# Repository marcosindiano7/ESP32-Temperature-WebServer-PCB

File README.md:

# ESP32 Temperature Web Server PCB

Custom two-layer PCB designed in KiCad for an ESP32-based temperature monitoring system.  
The board measures temperature using an LM35 analog sensor and allows the measured value to be monitored through a web interface served by the ESP32 module.

This project focuses on the complete hardware development flow: schematic capture, PCB layout, manufacturing files generation, board assembly and laboratory validation.

## Project Overview

The goal of this project was to design and validate a functional printed circuit board for an IoT temperature monitoring device.

The system includes:

- ESP32 module as the main processing and communication unit
- LM35 analog temperature sensor
- USB-to-UART interface based on CH340N
- RS232 communication interface
- Communication selection through jumpers
- 5 V regulated power supply stage
- Bootloader and reset management circuitry
- Alarm LED output
- Expansion connector for additional ESP32 signals
- Two-layer PCB designed in KiCad
- SMD and through-hole component assembly
- Laboratory functional validation

## PCB Preview

### 3D Render

### PCB Layout

### Assembled Board

### Web Interface

## Hardware Architecture

The schematic is divided into several functional blocks:

### Power Regulation

The power stage provides the regulated supply required by the system.  
It includes input filtering, a linear voltage regulator and a power indicator LED.

### ESP32 Module

The ESP32 module acts as the core of the system.  
It is connected to the temperature sensing stage, UART communication lines, boot/reset circuitry and alarm LED.

### Temperature Sensor

The board uses an LM35 analog temperature sensor.  
Its output voltage is proportional to the measured temperature and is connected to the ESP32 analog input through a simple conditioning/filtering stage.

### USB Interface

A CH340N USB-to-UART converter is used to provide serial communication through the USB connector.

### RS232 Interface

The board also includes an RS232 communication stage with level adaptation to interface with the ESP32 UART signals.

### Communication Selection

Jumpers are used to select whether the ESP32 UART lines are connected to the USB interface or to the RS232 interface.

### Bootloader and Reset Management

The design includes manual and automatic boot/reset circuitry, allowing the ESP32 to start normally or enter programming mode.

### Expansion Connector

An expansion connector exposes additional ESP32 pins for future extensions or external peripherals.

## Repository Structure

```text
.
├── hardware/
│   ├── kicad/              # KiCad project files
│   └── fabrication/        # Gerber and drill files
├── docs/
│   └── images/             # Schematic captures, PCB renders and photos
├── bom/                    # Bill of materials, if available
├── README.md
└── .gitignore
```

## KiCad Design

The hardware design was developed using KiCad and includes:

- Schematic capture
- Custom symbol/footprint handling
- Two-layer PCB layout
- Functional block-based component placement
- Top and bottom copper zones connected to GND
- SMD and through-hole component placement
- Mounting holes
- Silkscreen identification
- Design files ready for manufacturing

## Manufacturing Files

The `hardware/fabrication/` folder contains the production files required to manufacture the PCB:

- Top and bottom copper layers
- Top and bottom solder mask
- Top and bottom silkscreen
- Solder paste layers
- Board outline
- PTH and NPTH drill files
- Gerber job file

## Assembly

The PCB was manufactured externally and later assembled in the laboratory.  
The assembly process included both SMD and through-hole components.

Main assembled elements:

- ESP32 socket/header area
- USB connector
- DB9 RS232 connector
- Voltage regulator
- CH340N USB-to-UART converter
- LM35 temperature sensor socket
- BJTs and diode-based interface circuitry
- Jumpers and test points
- Indicator LEDs
- Mounting holes

## Validation

The assembled PCB was validated through several checks:

- Power supply verification
- 5 V regulator output measurement
- ESP32 module power-up test
- USB communication test
- RS232 communication test
- UART signal routing through jumpers
- Web server access from a mobile browser
- Temperature visualization
- Configurable threshold test
- Alarm LED activation when the temperature exceeds the configured threshold

## Functional Test

During the final test, the ESP32 web interface displayed:

- Current time
- Measured temperature
- Configurable temperature threshold
- Alarm message when the threshold was exceeded
- Button to clear the alert

Example web interface:

## Skills Demonstrated

- PCB design with KiCad
- Schematic capture
- PCB layout and routing
- Gerber and drill file generation
- SMD soldering
- Through-hole soldering
- ESP32-based IoT hardware
- Analog sensor integration
- USB-to-UART communication
- RS232 interface design
- Boot/reset circuit integration
- Laboratory hardware validation
- Multimeter and oscilloscope-based testing
- Technical documentation

## Notes

This repository focuses on the hardware design, PCB manufacturing files and validation process.  
Firmware or software not originally developed by the author is not included.

## Author

Marcos Indiano  
Electronic Communications Engineering student  
Universidad Politécnica de Madrid

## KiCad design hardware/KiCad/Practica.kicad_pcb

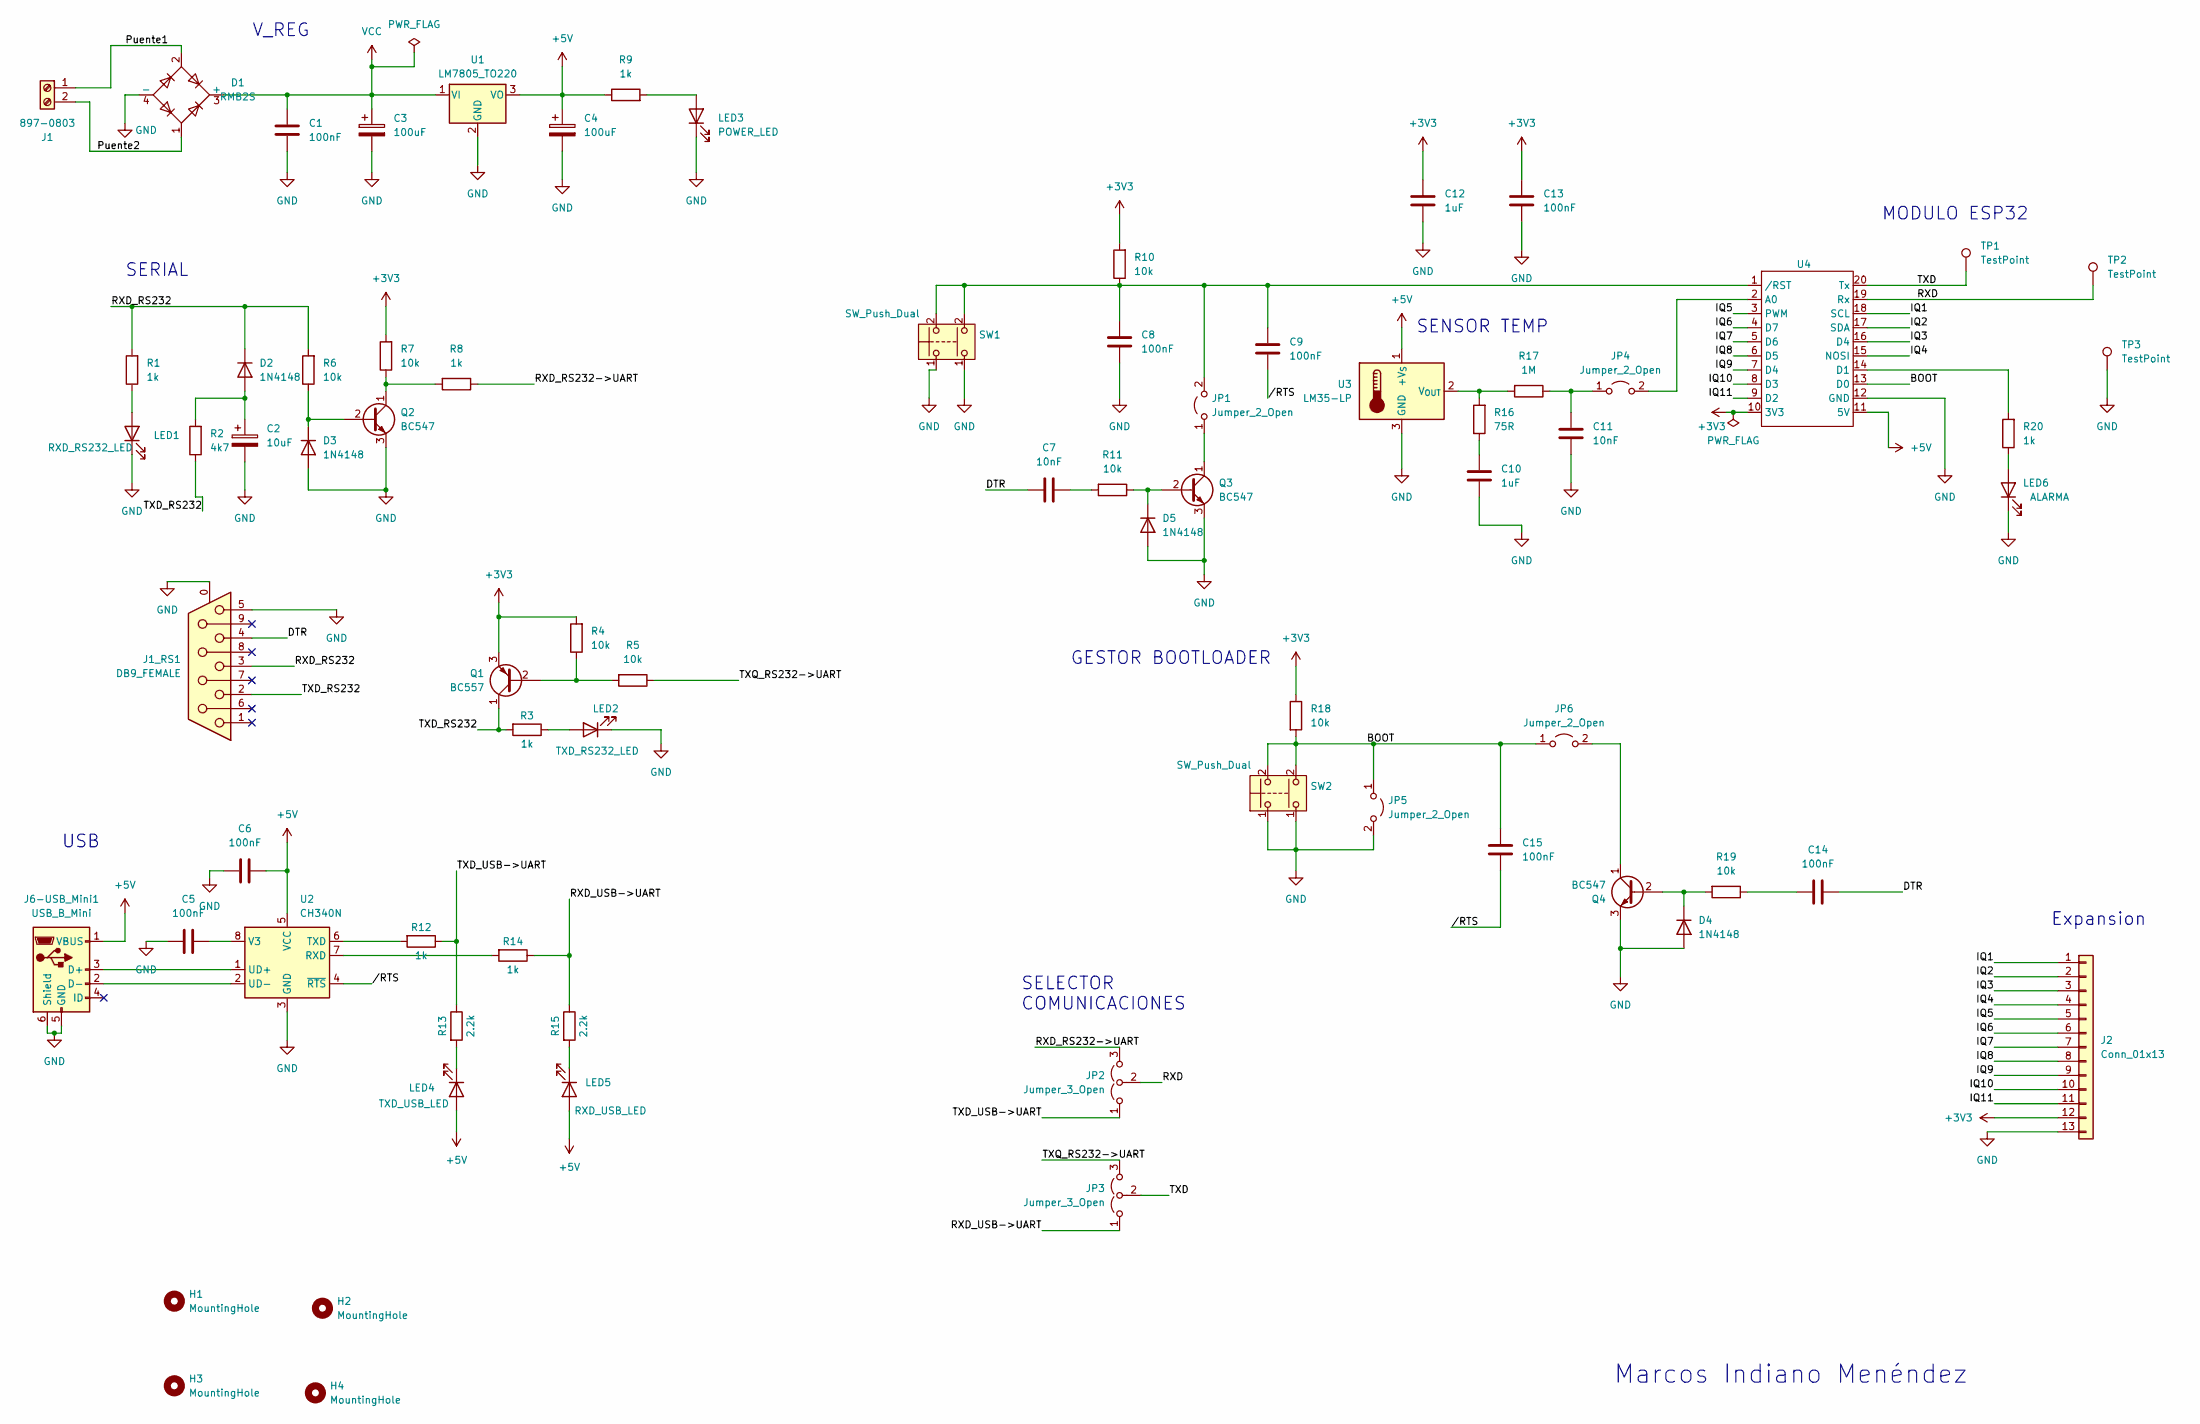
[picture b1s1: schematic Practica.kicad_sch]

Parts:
C1, C5, C6, C8, C9, C13, C14, C15: 100nF; C_1206_3216Metric
C2: 10uF; C_1206_3216Metric
C3, C4: 100uF; CP_Radial_D5.0mm_P2.50mm
C7, C11: 10nF; C_1206_3216Metric
C10, C12: 1uF; C_1206_3216Metric
D1: RMB2S; TO-269AA
D2, D3, D4, D5: 1N4148; D_DO-35_SOD27_P7.62mm_Horizontal
H1, H2, H3, H4: MountingHole; MountingHole_3mm_Pad
J1: 897-0803; TerminalBlock_RND_205-00276_1x02_P5.00mm_Vertical
J1_RS1: DB9_FEMALE; DSUB-9_Female_Horizontal_P2.77x2.84mm_EdgePinOffset4.94mm_H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
J2: Conn_01x13; PinHeader_1x13_P2.54mm_Vertical
J6-USB_Mini1: USB_B_Mini; USB_Mini-B_Wuerth_65100516121_Horizontal
JP1, JP4, JP5, JP6: Jumper_2_Open; PinHeader_1x02_P2.54mm_Vertical
JP2, JP3: Jumper_3_Open; PinHeader_1x03_P2.54mm_Vertical
LED1: RXD_RS232_LED; LED_D3.0mm
LED2: TXD_RS232_LED; LED_D3.0mm
LED3: POWER_LED; LED_D3.0mm
LED4: TXD_USB_LED; LED_D3.0mm
LED5: RXD_USB_LED; LED_D3.0mm
LED6: ALARMA; LED_D3.0mm
Q1: BC557; TO-92_Inline
Q2, Q3, Q4: BC547; TO-92_Inline_Wide
R1, R3, R8, R9, R12, R14, R20: 1k; R_1206_3216Metric
R2: 4k7; R_1206_3216Metric
R4, R5, R6, R7, R10, R11, R18, R19: 10k; R_1206_3216Metric
R13, R15: 2.2k; R_1206_3216Metric
R16: 75R; R_1206_3216Metric
R17: 1M; R_1206_3216Metric
SW1, SW2: SW_Push_Dual; SW_SPST_B3S-1000
TP1, TP2, TP3: TestPoint; TestPoint_THTPad_1.5x1.5mm_Drill0.7mm
U1: LM7805_TO220; TO-220-3_Vertical
U2: CH340N; SOP-8_3.9x4.9mm_P1.27mm
U3: LM35-LP; TO-92_Inline_Wide
U4: ESP32

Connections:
+3V3: C12.1, C13.1, J2.12, Q1.3 (E), R4.2, R7.2, R10.2, R18.1, U4.10 (3V3)
+5V: C4.1, C6.2, J6-USB_Mini1.1 (VBUS), LED4.2 (A), LED5.2 (A), R9.1, U1.3 (VO), U2.5 (VCC), U3.1 (+V_{S}), U4.11 (5V)
/BOOT: C15.2, JP5.1 (A), JP6.1 (A), R18.2, SW2.2 (4), U4.13 (D0)
/DTR: C7.1, C14.2, J1_RS1.4
/IQ1: J2.1, U4.18 (SCL)
/IQ2: J2.2, U4.17 (SDA)
/IQ3: J2.3, U4.16 (D4)
/IQ4: J2.4, U4.15 (NOSI)
/IQ5: J2.5, U4.3 (PWM)
/IQ6: J2.6, U4.4 (D7)
/IQ7: J2.7, U4.5 (D6)
/IQ8: J2.8, U4.6 (D5)
/IQ9: J2.9, U4.7 (D4)
/IQ10: J2.10, U4.8 (D3)
/IQ11: J2.11, U4.9 (D2)
/Puente1: D1.2, J1.1
/Puente2: D1.1, J1.2
/RXD: JP2.2 (C), TP2.1, U4.19 (Rx)
/RXD_RS232: D2.1 (K), J1_RS1.3, R1.2, R6.2
/RXD_RS232->UART: JP2.3 (B), R8.1
/RXD_USB->UART: JP3.1 (A), R14.1, R15.1
/TXD: JP3.2 (C), TP1.1, U4.20 (Tx)
/TXD_RS232: J1_RS1.2, Q1.1 (C), R2.1, R3.2
/TXD_USB->UART: JP2.1 (A), R12.1, R13.1
/TXQ_RS232->UART: JP3.3 (B), R5.1
//RTS: C9.2, C15.1, U2.4 (~RTS)
GND: C1.2, C2.2, C3.2, C4.2, C5.1, C6.1, C8.2, C10.2, C11.2, C12.2, C13.2, D1.4 (-), D3.2 (A), D4.2 (A), D5.2 (A), J1_RS1.0 (PAD), J1_RS1.5, J2.13, J6-USB_Mini1.5 (GND), J6-USB_Mini1.6 (Shield), JP5.2 (B), LED1.1 (K), LED2.1 (K), LED3.1 (K), LED6.1 (K), Q2.3 (E), Q3.3 (E), Q4.3 (E), SW1.1, SW2.1, TP3.1, U1.2 (GND), U2.3 (GND), U3.3 (GND), U4.12 (GND)
unnamed: C7.2, R11.2
unnamed: C10.1, R16.1
unnamed: C14.1, R19.1
unnamed: C2.1, D2.2 (A), R2.2
unnamed: D3.1 (K), Q2.2 (B), R6.1
unnamed: D4.1 (K), Q4.2 (B), R19.2
unnamed: D5.1 (K), Q3.2 (B), R11.1
unnamed: J6-USB_Mini1.3 (D+), U2.1 (UD+)
unnamed: J6-USB_Mini1.2 (D-), U2.2 (UD-)
unnamed: JP1.1 (A), Q3.1 (C)
unnamed: C8.1, C9.1, JP1.2 (B), R10.1, SW1.2, U4.1 (/RST)
unnamed: C11.1, JP4.1 (A), R17.1
unnamed: JP4.2 (B), U4.2 (A0)
unnamed: JP6.2 (B), Q4.1 (C)
unnamed: LED1.2 (A), R1.1
unnamed: LED2.2 (A), R3.1
unnamed: LED3.2 (A), R9.2
unnamed: LED4.1 (K), R13.2
unnamed: LED5.1 (K), R15.2
unnamed: LED6.2 (A), R20.1
unnamed: Q1.2 (B), R4.1, R5.2
unnamed: Q2.1 (C), R7.1, R8.2
unnamed: R14.2, U2.7 (RXD)
unnamed: R12.2, U2.6 (TXD)
unnamed: C5.2, U2.8 (V3)
unnamed: R16.2, R17.2, U3.2 (V_{OUT})
unnamed: R20.2, U4.14 (D1)
VCC: C1.1, C3.1, D1.3 (+), U1.1 (VI)

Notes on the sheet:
SELECTOR COMUNICACIONES
SERIAL
Marcos Indiano Menéndez
SENSOR TEMP
Expansion
USB
V_REG
MODULO ESP32
GESTOR BOOTLOADER

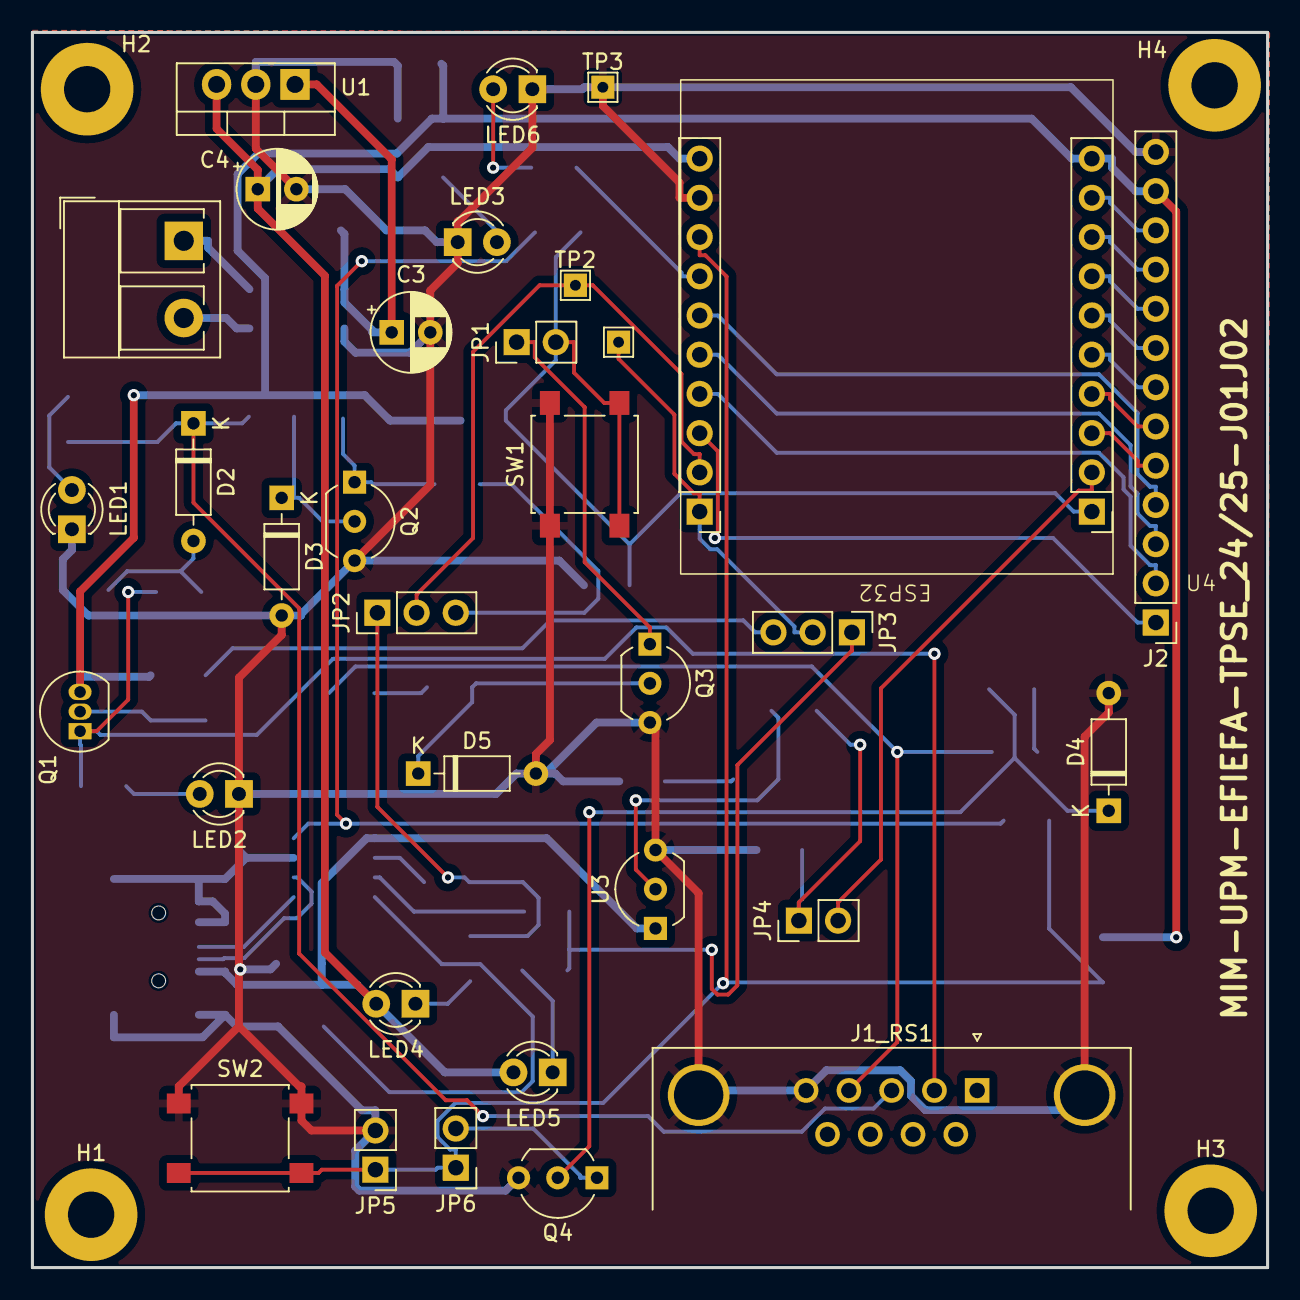
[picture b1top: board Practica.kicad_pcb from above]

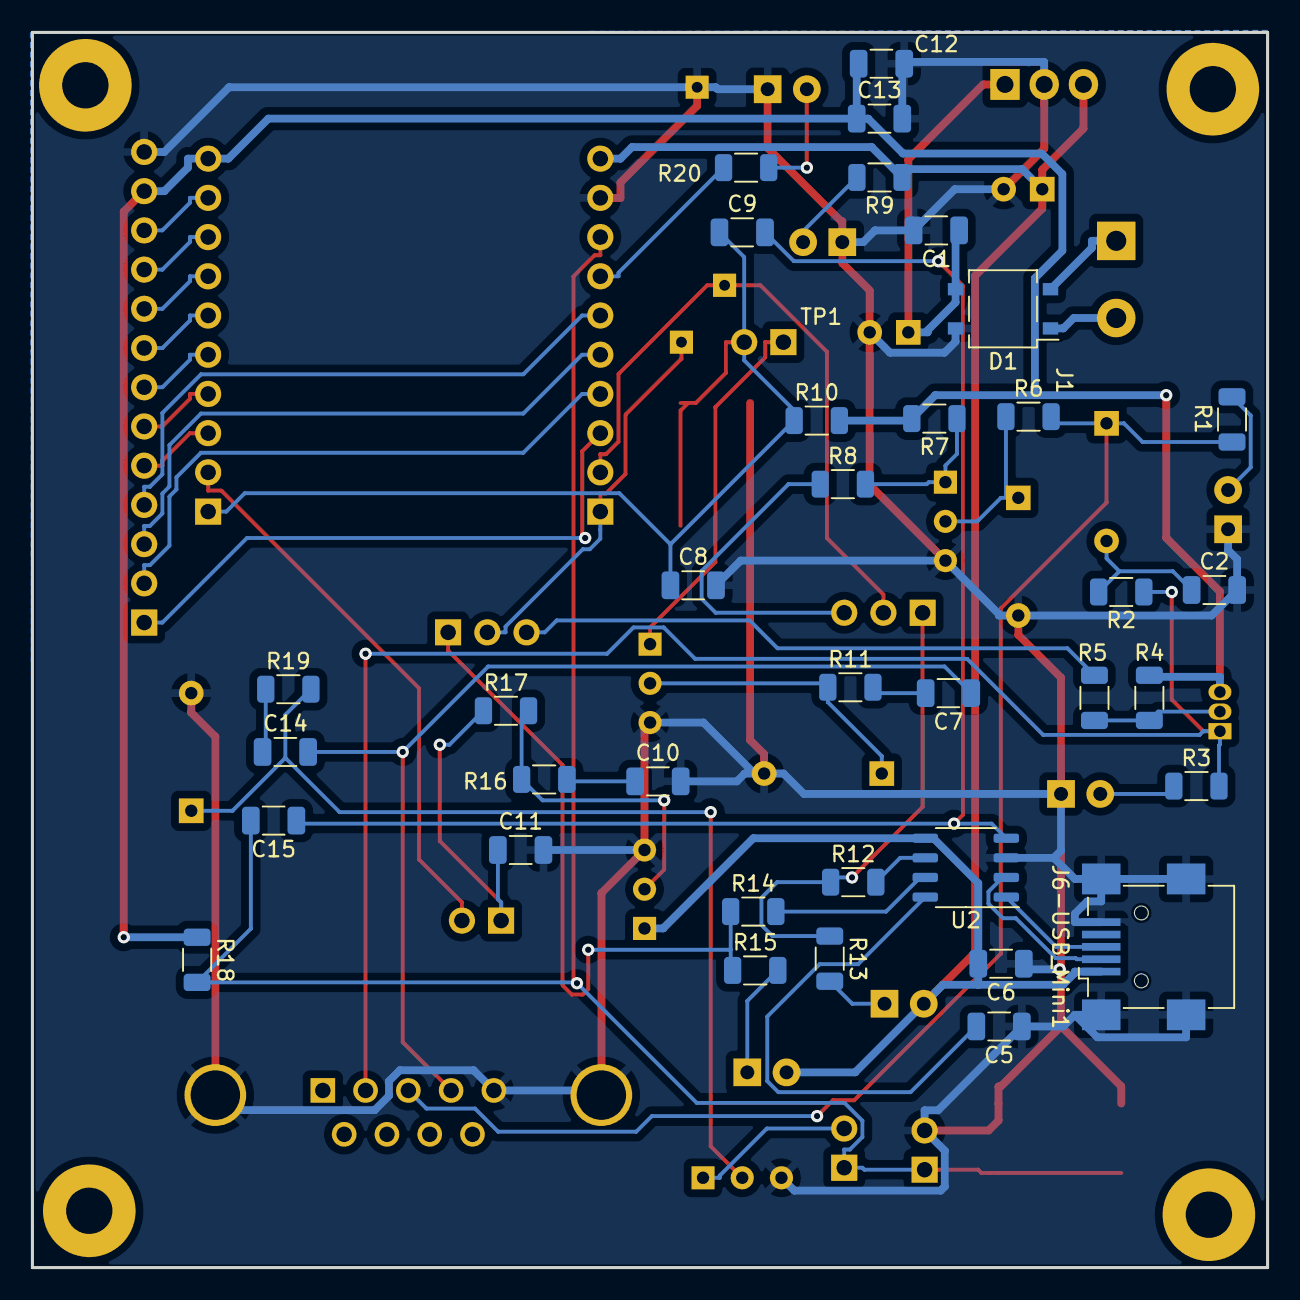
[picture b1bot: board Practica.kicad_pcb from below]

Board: 2 copper layers, 80.0 x 80.0 mm, 73 parts (36 on the bottom side), 55 nets.

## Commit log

2026-05-11 ESP32-Temperature-WebServer-PCB proyect
2026-05-11 Add README for ESP32 Temperature Web Server PCB
    Added detailed project documentation for the ESP32 Temperature Web Server PCB, including hardware architecture, validation process, and skills demonstrated.
